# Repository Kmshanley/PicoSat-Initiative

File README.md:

# PicoSat-Initiative

The Wentworth Picosat initiative is a group at Wentworth Institute of technology dedicated to making a pocket cube satellite capable of earth observation from LEO.

The pocket cube standard requires satellites to be 5x5x5cm and under 250 grams. Upon completion of this Wentworth PicoSat it will become one of the smallest satellites capable of high resolution imagery from LEO.

* **Homepage:** <https://picosat.notion.site>
* **Communication:** <https://discord.gg/C9kFq642a>

Organization
------------------------
This repository is divided into two primary sections:
### Test
> Contains all firmware related to testing boards or individual components.
### Flight
> Contains the development for the main flight firmware that will be deployed in space.

Getting Started
------------------------
The easiest way to get started is by using the Stm32CubeIDE.

Downloadable here: https://www.st.com/en/development-tools/stm32cubeide.html

From here you should be able to import the various project files (.ioc) and CubeIDE will handle setup, build tools, and compilation.

High Level Overview
------------------------

The Satellite is composed of several **subsystems**:

* Onboard Computer System (OBC)
    * Responsible for handling commands from the ground station
    * Running ADCS algorithms
    * Commanding the image sensor to take pictures
        * Compressing and Storing these pictures until downlink
    * Gathering telemetry from sensors
        * Feeding telemetry to the appropriate subsystem
            * I.e. LUX sensor data to ADCS
    * Managing Satellite Energy consumption
        * Monitoring battery health and determining wakeup periods
* Electrical Power System (EPS)
    * Responsible for generating, storing, and regulating electrical power
* Communications (COMMS)
    * Responsible for uplink and downlink to ground station 
* Attitude Control and determination (ADCS)
    * Responsible for determining the attitude (rotation) of the satellite
    * Responsible for executing rotational maneuvers

Hardware Overview
------------------------

Contact
------------------------
You can join our discord with the link above or contact us directly via email:

OBC Team Lead (Kieran Shanley): <kmshanley01@gmail.com>

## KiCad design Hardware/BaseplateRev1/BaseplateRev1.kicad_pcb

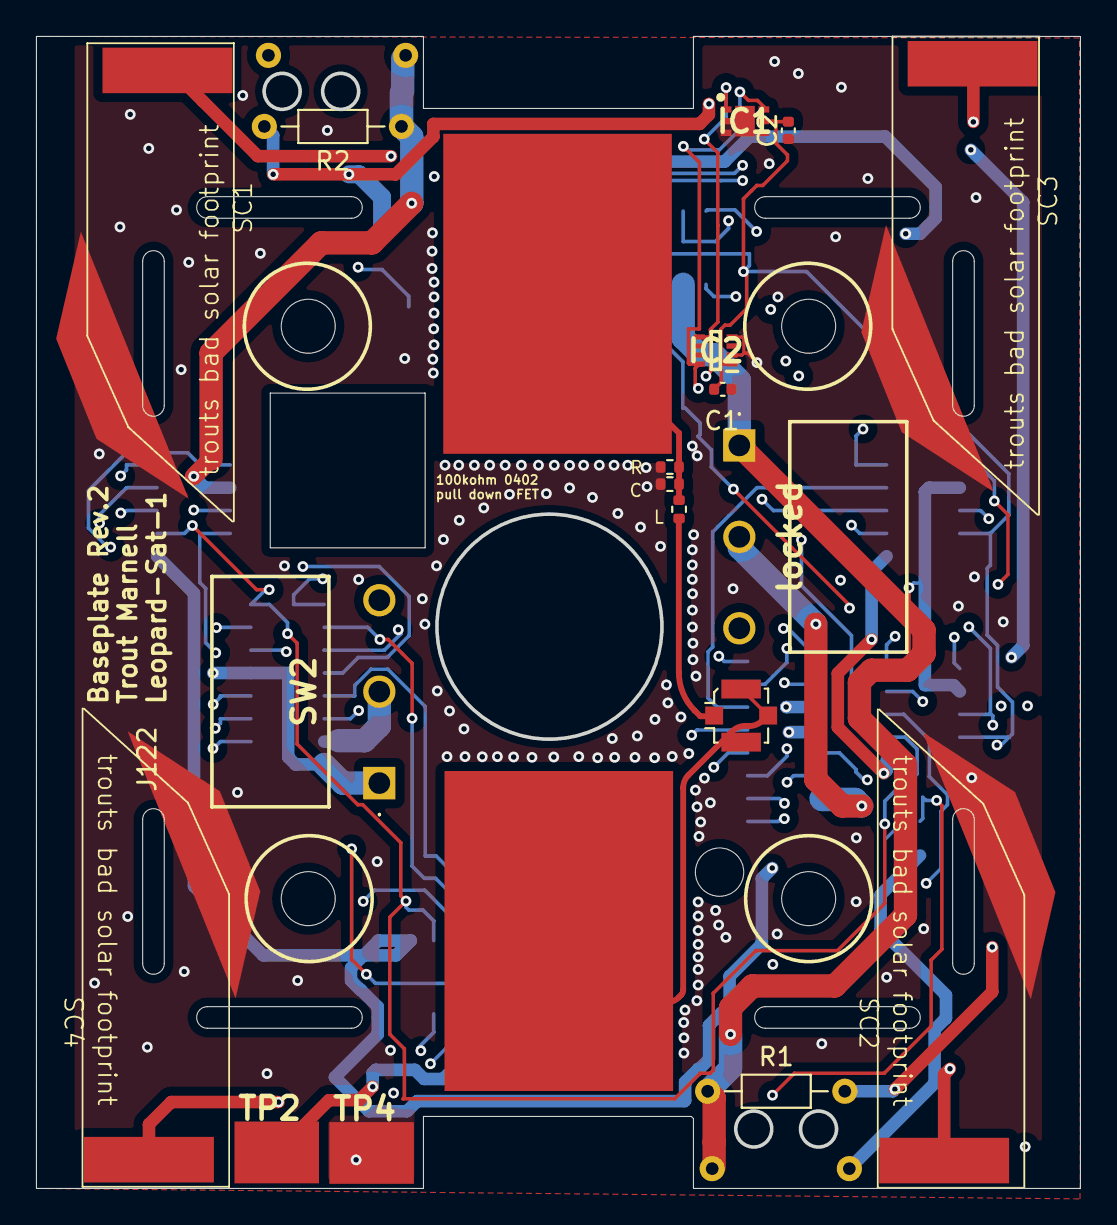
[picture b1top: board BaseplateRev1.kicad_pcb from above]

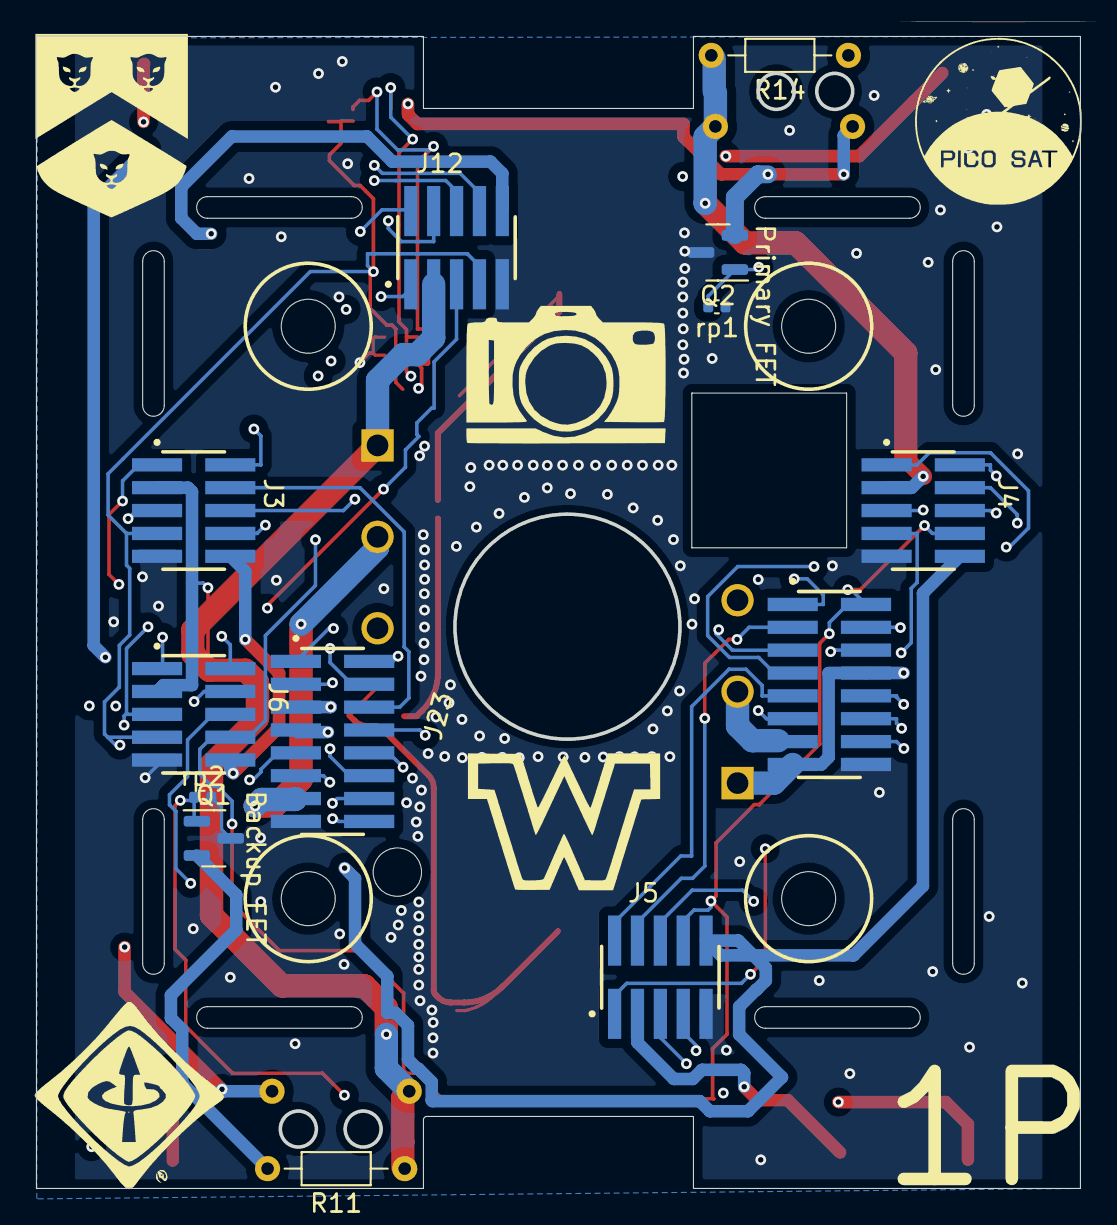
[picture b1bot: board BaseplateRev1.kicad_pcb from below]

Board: 4 copper layers, 57.9 x 63.9 mm, 33 parts (13 on the bottom side), 33 nets.

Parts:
C1, C2: 0.1uF; C_0402_1005Metric
IC1: TMP117MAIDRVR; SON65P200X200X80-7N
IC2: OPT4048DTSR; SOTFL50P190X60-8N
J3, J4, J5, J6, J12: FTSH-105-XX-X-DV; SAMTEC_FTSH-105-XX-X-DV
J8: Conn_Coaxial; U.FL_Molex_MCRF_73412-0110_Vertical
J23, J122: FLE-108-01-XX-DV; SAMTEC_FW-08-03-G-D-335-065
Q1, Q2: 2N7002; SOT-23
R1, R2, R11, R14: R_Small_US; R_Axial_DIN0204_L3.6mm_D1.6mm_P7.62mm_Horizontal
REF5554: R_0402_1005Metric
REFW: R_0402_1005Metric
REFinduc: R_0402_1005Metric
SC1, SC2, SC3, SC4: Solar_Cell; solar
SW2: SW_SPDT; D2FA1
TP2, TP4: TestPoint; 5016
U1, U2: antenna
locked: SW_SPDT; D2FA1
rp1, rp2: 100k; C_0402_1005Metric

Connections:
1.8V: C1.2, C2.2, IC1.5 (V+), IC2.1 (VDD), J3.07, J4.07, J5.07, J6.07, J12.07, J23.11, J122.14
Battery +: J3.03, J4.03, J5.03, J6.03, J12.03, J122.08, J122.15, R1.1, R2.1, R11.1, R14.2, SW2.1 (A), TP2.1, locked.1 (A)
Coaxout: J8.1 (In), REFinduc.1
DRV ENABLE 1: J4.04, J122.01
DRV ENABLE 2: J5.04, J122.03
DRV ENABLE 3: J6.04, J23.10
DRV ENABLE 4: J12.04, J23.08
DRV ENABLE 5: J3.04, J23.06
GND: C1.1, C2.1, IC1.2 (GND), IC1.3 (ALERT), IC1.4 (ADD0), IC1.7 (EP), IC2.2 (ADDR), IC2.4 (GND), J3.09, J4.09, J5.09, J6.09, J12.09, J23.15, J122.16, Q1.3 (D), Q2.3 (D), REF5554.1, REFW.1, SC1.2 (-), SC2.2 (-), SC3.2 (-), SC4.2 (-), TP4.1, rp1.1, rp2.2
MCU ENABLE 1: J122.07, Q2.1 (G), rp1.2
MCU ENABLE 2: J122.05, Q1.1 (G), rp2.1
MPPT ENABLE: J3.06, J4.06, J5.06, J6.06, J12.06, J122.06
unnamed: Q1.2 (S), R11.2, R14.1
unnamed: Q2.2 (S), R1.2, R2.2
PWM1(1): J4.01, J122.10
PWM1(2): J5.01, J122.11
PWM1(3): J6.01, J23.02
PWM1(4): J12.01, J23.03
PWM1(5): J3.01, J23.09
PWM2(1): J4.02, J122.12
PWM2(2): J5.02, J122.09
PWM2(3): J6.02, J23.04
PWM2(4): J12.02, J23.01
PWM2(5): J3.02, J23.16
RF ANTENNA: REF5554.2, REFW.2, REFinduc.2, U2.1 (RF_IN)
SCL(1): J4.08, J5.08, J6.08, J12.08, J122.02
SCL(2): IC1.1 (SCL), IC2.5 (SCL), J3.08, J23.12
SDA(1): J4.05, J5.05, J6.05, J12.05, J122.04
SDA(2): IC1.6 (SDA), IC2.8 (SDA), J3.05, J23.14
VBAT+: J23.13, J122.13, SW2.2 (B), locked.2 (B)
VMPPT: J3.10, J4.10, J5.10, J6.10, J12.10, J23.07
Vsolar: J23.05, SC1.1 (+), SC2.1 (+), SC3.1 (+), SC4.1 (+)
rfgnd: J8.2 (Ext), U1.1 (RF_IN)

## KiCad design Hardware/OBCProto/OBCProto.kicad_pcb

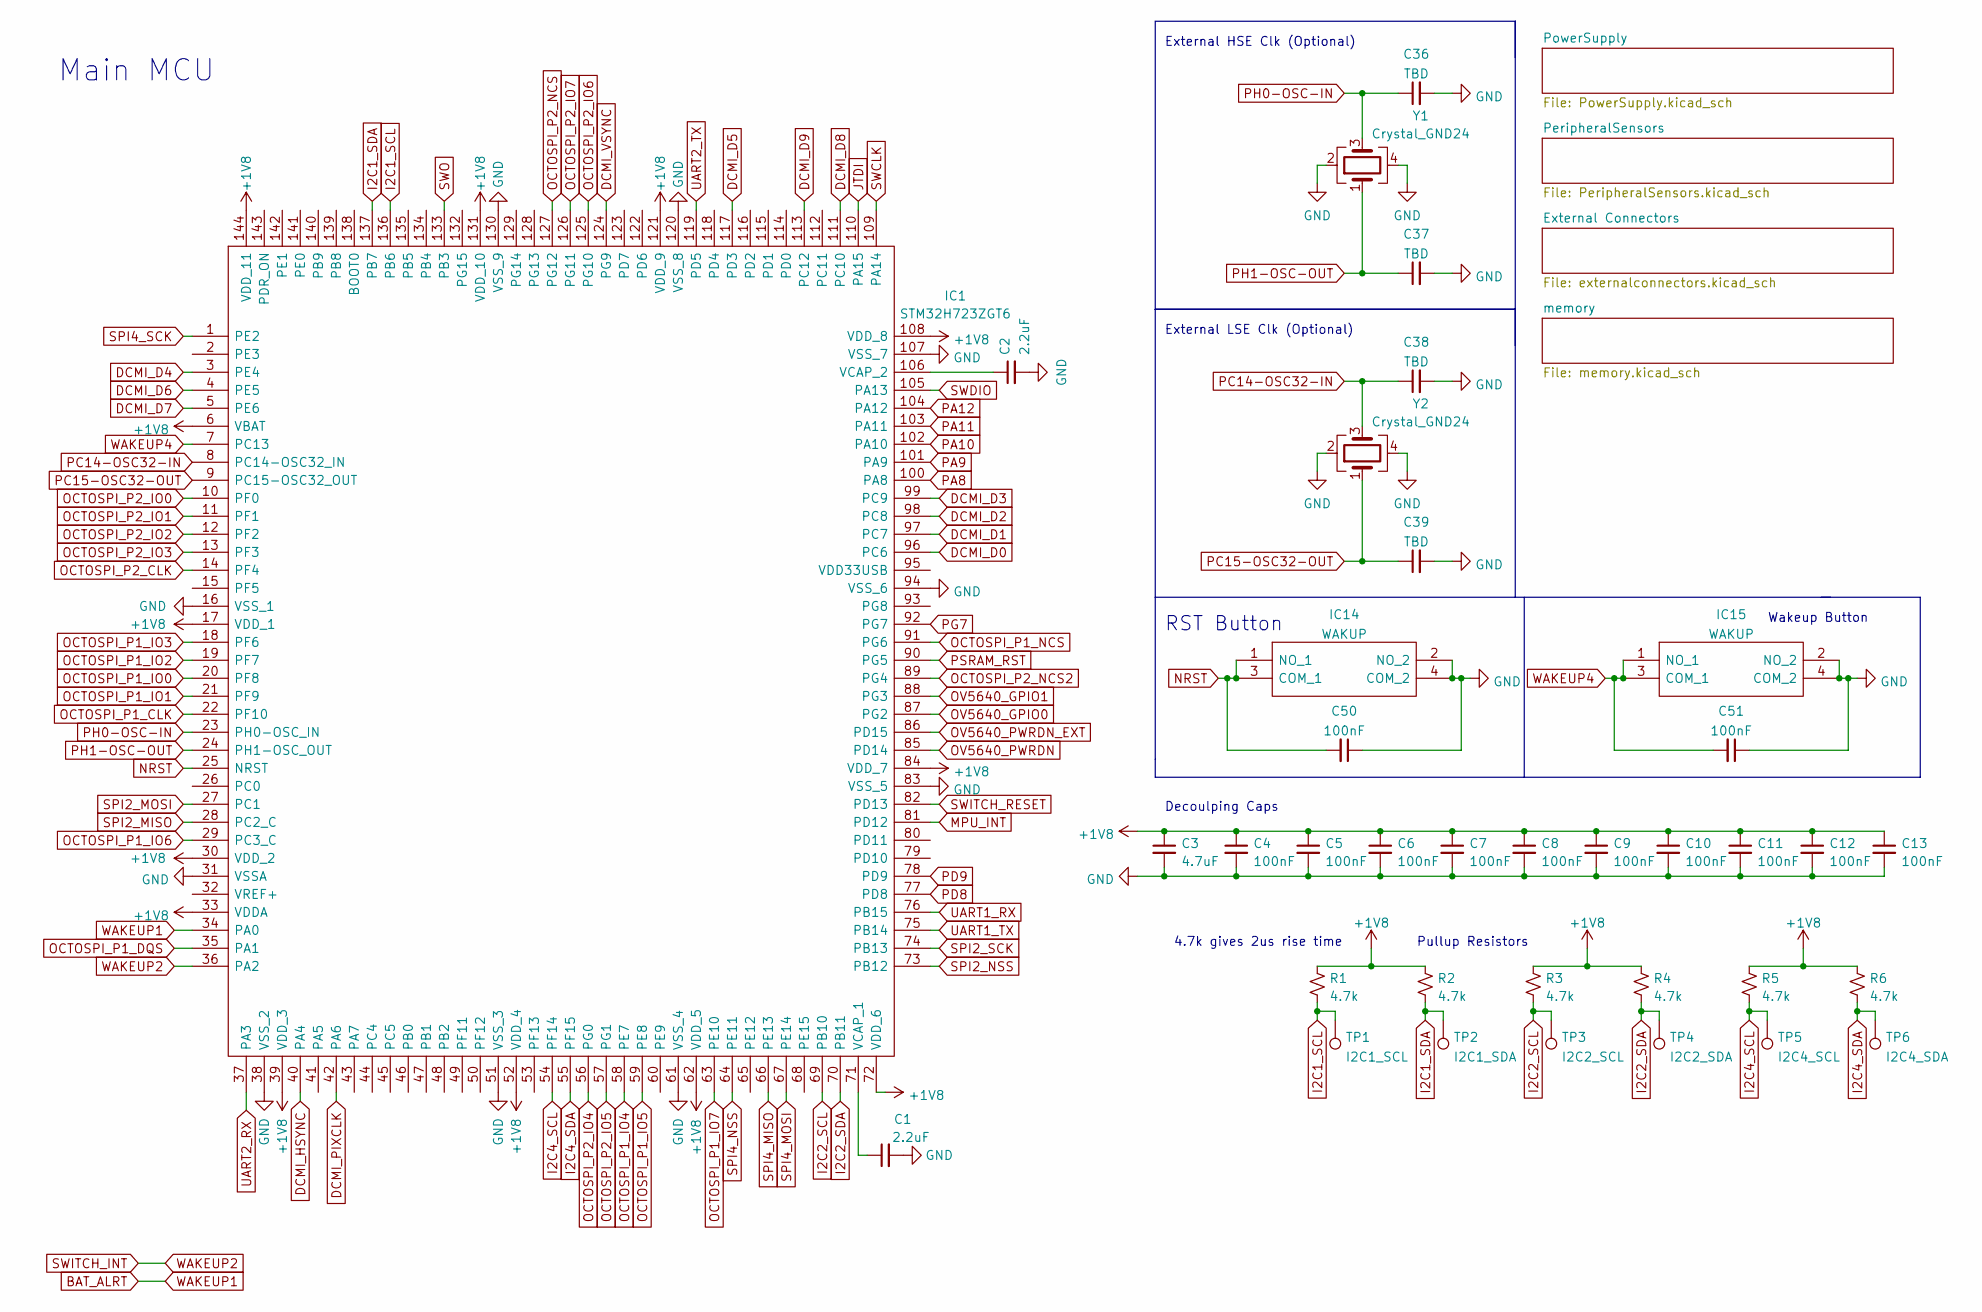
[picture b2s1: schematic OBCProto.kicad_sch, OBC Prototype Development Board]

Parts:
C1, C2: 2.2uF; C_0402_1005Metric
C3: 4.7uF; C_0402_1005Metric
C4, C5, C6, C7, C8, C9, C10, C11, C12, C13, C50, C51: 100nF; C_0402_1005Metric
C36, C37, C38, C39: TBD; C_0402_1005Metric
IC1: STM32H723ZGT6; QFP50P2200X2200X160-144N; Mouser Part Number 511-STM32H723ZGT6
IC14, IC15: WAKUP; TS046675BK160SMT; Mouser Part Number 179-TS046675BK160SMT
R1, R2, R3, R4, R5, R6: 4.7k; R_0402_1005Metric
TP1: I2C1_SCL; TestPoint_Pad_2.0x2.0mm
TP2: I2C1_SDA; TestPoint_Pad_2.0x2.0mm
TP3: I2C2_SCL; TestPoint_Pad_2.0x2.0mm
TP4: I2C2_SDA; TestPoint_Pad_2.0x2.0mm
TP5: I2C4_SCL; TestPoint_Pad_2.0x2.0mm
TP6: I2C4_SDA; TestPoint_Pad_2.0x2.0mm
Y1, Y2: Crystal_GND24; Crystal_SMD_2520-4Pin_2.5x2.0mm

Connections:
+1V8: C3.1, C4.1, C5.1, C6.1, C7.1, C8.1, C9.1, C10.1, C11.1, C12.1, C13.1, IC1.6 (VBAT), IC1.17 (VDD_1), IC1.30 (VDD_2), IC1.33 (VDDA), IC1.39 (VDD_3), IC1.52 (VDD_4), IC1.62 (VDD_5), IC1.72 (VDD_6), IC1.84 (VDD_7), IC1.108 (VDD_8), IC1.121 (VDD_9), IC1.131 (VDD_10), IC1.144 (VDD_11), R1.1, R2.1, R3.1, R4.1, R5.1, R6.1; also elsewhere on the board
BAT_ALRT: IC1.34 (PA0)
DCMI_D0: IC1.96 (PC6); also elsewhere on the board
DCMI_D1: IC1.97 (PC7); also elsewhere on the board
DCMI_D2: IC1.98 (PC8); also elsewhere on the board
DCMI_D3: IC1.99 (PC9); also elsewhere on the board
DCMI_D4: IC1.3 (PE4); also elsewhere on the board
DCMI_D5: IC1.117 (PD3); also elsewhere on the board
DCMI_D6: IC1.4 (PE5); also elsewhere on the board
DCMI_D7: IC1.5 (PE6); also elsewhere on the board
DCMI_D8: IC1.111 (PC10); also elsewhere on the board
DCMI_D9: IC1.113 (PC12); also elsewhere on the board
DCMI_HSYNC: IC1.40 (PA4); also elsewhere on the board
DCMI_PIXCLK: IC1.42 (PA6); also elsewhere on the board
DCMI_VSYNC: IC1.124 (PG9); also elsewhere on the board
GND: C1.2, C2.2, C3.2, C4.2, C5.2, C6.2, C7.2, C8.2, C9.2, C10.2, C11.2, C12.2, C13.2, C36.2, C37.2, C38.2, C39.2, C50.1, C51.1, IC1.16 (VSS_1), IC1.31 (VSSA), IC1.38 (VSS_2), IC1.51 (VSS_3), IC1.61 (VSS_4), IC1.83 (VSS_5), IC1.94 (VSS_6), IC1.107 (VSS_7), IC1.120 (VSS_8), IC1.130 (VSS_9), IC14.2 (NO_2), IC14.4 (COM_2), IC15.2 (NO_2), IC15.4 (COM_2), Y1.2, Y1.4, Y2.2, Y2.4; also elsewhere on the board
I2C1_SCL: IC1.136 (PB6), R1.2, TP1.1; also elsewhere on the board
I2C1_SDA: IC1.137 (PB7), R2.2, TP2.1; also elsewhere on the board
I2C2_SCL: IC1.69 (PB10), R3.2, TP3.1; also elsewhere on the board
I2C2_SDA: IC1.70 (PB11), R4.2, TP4.1; also elsewhere on the board
I2C4_SCL: IC1.54 (PF14), R5.2, TP5.1; also elsewhere on the board
I2C4_SDA: IC1.55 (PF15), R6.2, TP6.1; also elsewhere on the board
JTDI: IC1.110 (PA15); also elsewhere on the board
MPU_INT: IC1.81 (PD12); also elsewhere on the board
NRST: C50.2, IC1.25 (NRST), IC14.1 (NO_1), IC14.3 (COM_1); also elsewhere on the board
unnamed: C1.1, IC1.71 (VCAP_1)
unnamed: C2.1, IC1.106 (VCAP_2)
OCTOSPI_P1_CLK: IC1.22 (PF10); also elsewhere on the board
OCTOSPI_P1_DQS: IC1.35 (PA1); also elsewhere on the board
OCTOSPI_P1_IO0: IC1.20 (PF8); also elsewhere on the board
OCTOSPI_P1_IO1: IC1.21 (PF9); also elsewhere on the board
OCTOSPI_P1_IO2: IC1.19 (PF7); also elsewhere on the board
OCTOSPI_P1_IO3: IC1.18 (PF6); also elsewhere on the board
OCTOSPI_P1_IO4: IC1.58 (PE7); also elsewhere on the board
OCTOSPI_P1_IO5: IC1.59 (PE8); also elsewhere on the board
OCTOSPI_P1_IO6: IC1.29 (PC3_C); also elsewhere on the board
OCTOSPI_P1_IO7: IC1.63 (PE10); also elsewhere on the board
OCTOSPI_P1_NCS: IC1.91 (PG6); also elsewhere on the board
OCTOSPI_P2_CLK: IC1.14 (PF4); also elsewhere on the board
OCTOSPI_P2_IO0: IC1.10 (PF0); also elsewhere on the board
OCTOSPI_P2_IO1: IC1.11 (PF1); also elsewhere on the board
OCTOSPI_P2_IO2: IC1.12 (PF2); also elsewhere on the board
OCTOSPI_P2_IO3: IC1.13 (PF3); also elsewhere on the board
OCTOSPI_P2_IO4: IC1.56 (PG0); also elsewhere on the board
OCTOSPI_P2_IO5: IC1.57 (PG1); also elsewhere on the board
OCTOSPI_P2_IO6: IC1.125 (PG10); also elsewhere on the board
OCTOSPI_P2_IO7: IC1.126 (PG11)
OCTOSPI_P2_NCS: IC1.127 (PG12); also elsewhere on the board
OCTOSPI_P2_NCS2: IC1.89 (PG4); also elsewhere on the board
OV5640_GPIO0: IC1.87 (PG2); also elsewhere on the board
OV5640_GPIO1: IC1.88 (PG3); also elsewhere on the board
OV5640_PWRDN: IC1.85 (PD14); also elsewhere on the board
OV5640_PWRDN_EXT: IC1.86 (PD15); also elsewhere on the board
PA8: IC1.100 (PA8); also elsewhere on the board
PA9: IC1.101 (PA9); also elsewhere on the board
PA10: IC1.102 (PA10); also elsewhere on the board
PA11: IC1.103 (PA11); also elsewhere on the board
PA12: IC1.104 (PA12); also elsewhere on the board
PC14-OSC32-IN: C38.1, IC1.8 (PC14-OSC32_IN), Y2.3
PC15-OSC32-OUT: C39.1, IC1.9 (PC15-OSC32_OUT), Y2.1
PD8: IC1.77 (PD8); also elsewhere on the board
PD9: IC1.78 (PD9); also elsewhere on the board
PG7: IC1.92 (PG7); also elsewhere on the board
PH0-OSC-IN: C36.1, IC1.23 (PH0-OSC_IN), Y1.3
PH1-OSC-OUT: C37.1, IC1.24 (PH1-OSC_OUT), Y1.1
PSRAM_RST: IC1.90 (PG5); also elsewhere on the board
SPI2_MISO: IC1.28 (PC2_C); also elsewhere on the board
SPI2_MOSI: IC1.27 (PC1); also elsewhere on the board
SPI2_NSS: IC1.73 (PB12); also elsewhere on the board
SPI2_SCK: IC1.74 (PB13); also elsewhere on the board
SPI4_MISO: IC1.66 (PE13); also elsewhere on the board
SPI4_MOSI: IC1.67 (PE14); also elsewhere on the board
SPI4_NSS: IC1.64 (PE11); also elsewhere on the board
SPI4_SCK: IC1.1 (PE2); also elsewhere on the board
SWCLK: IC1.109 (PA14); also elsewhere on the board
SWDIO: IC1.105 (PA13); also elsewhere on the board
SWITCH_INT: IC1.36 (PA2); also elsewhere on the board
SWITCH_RESET: IC1.82 (PD13); also elsewhere on the board
SWO: IC1.133 (PB3); also elsewhere on the board
UART1_RX: IC1.76 (PB15); also elsewhere on the board
UART1_TX: IC1.75 (PB14); also elsewhere on the board
UART2_RX: IC1.37 (PA3); also elsewhere on the board
UART2_TX: IC1.119 (PD5); also elsewhere on the board
WAKEUP4: C51.2, IC1.7 (PC13), IC15.1 (NO_1), IC15.3 (COM_1)

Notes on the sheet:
Main MCU
RST Button
Wakeup Button
4.7k gives 2us rise time
Pullup Resistors
External HSE Clk (Optional)
External LSE Clk (Optional)
Decoulping Caps

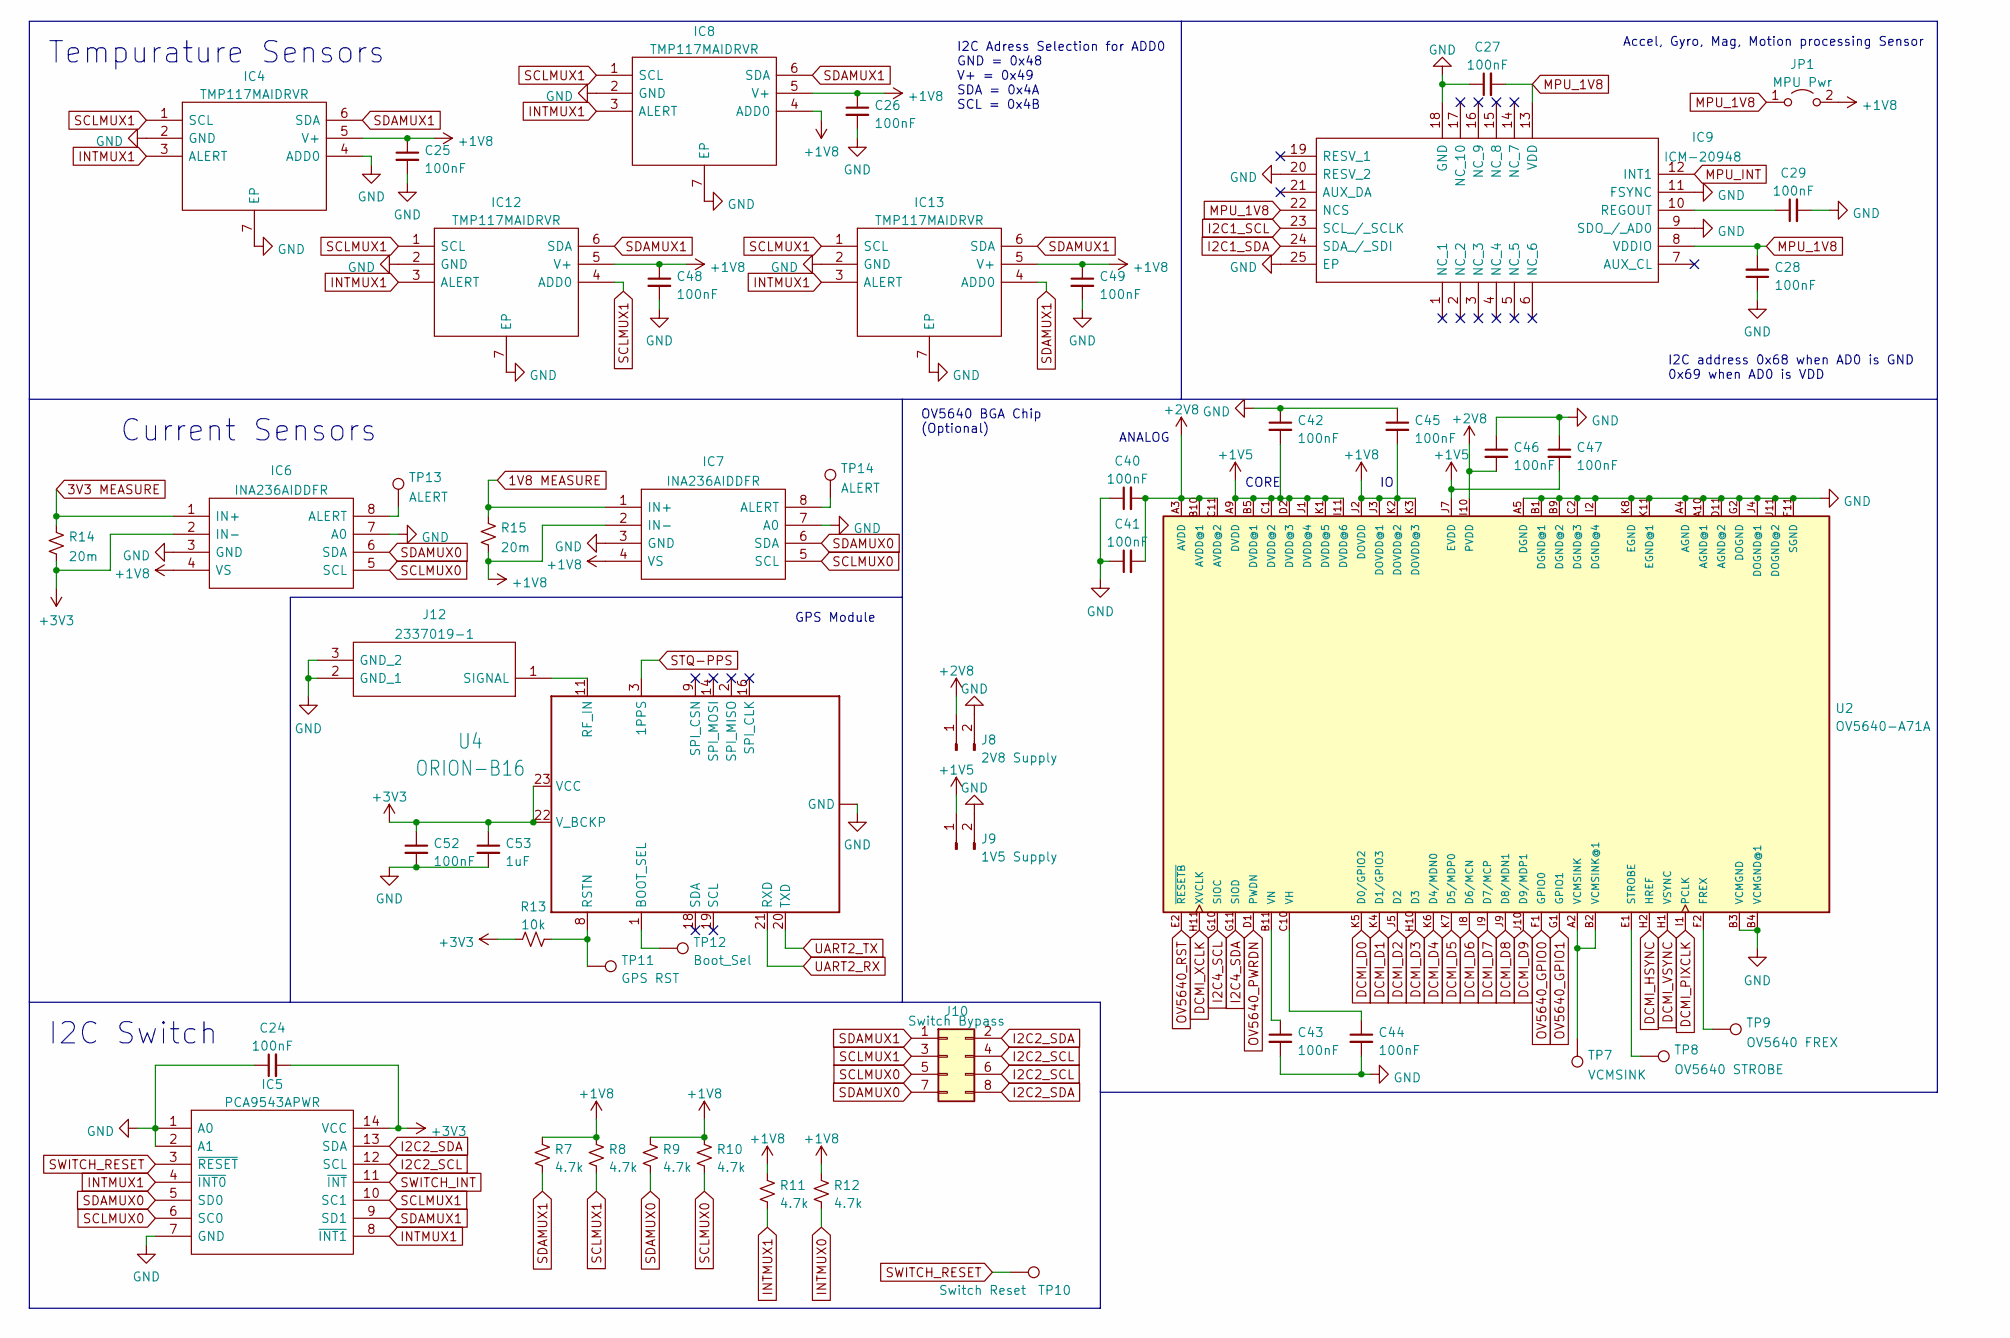
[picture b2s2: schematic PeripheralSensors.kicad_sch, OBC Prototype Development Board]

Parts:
C24, C25, C26, C27, C28, C29, C40, C41, C42, C43, C44, C45, C46, C47, C48, C49, C52: 100nF; C_0402_1005Metric
C53: 1uF; C_0402_1005Metric
IC4, IC8, IC12, IC13: TMP117MAIDRVR; SON65P200X200X80-7N; Mouser Part Number 595-TMP117MAIDRVR
IC5: PCA9543APWR; SOP65P640X120-14N; Mouser Part Number 595-PCA9543APWR
IC6, IC7: INA236AIDDFR; SOP65P280X110-8N; Manufacturer_Part_Number INA236AIDDFR; Mouser Part Number 595-INA236AIDDFR
IC9: ICM-20948; QFN40P300X300X105-25N-D; Mouser Part Number 410-ICM-20948
J8: 2V8 Supply; PinHeader_1x02_P2.54mm_Vertical
J9: 1V5 Supply; PinHeader_1x02_P2.54mm_Vertical
J10: Switch Bypass; PinHeader_2x04_P2.54mm_Vertical
J12: 2337019-1; 23370191; Mouser Part Number 571-2337019-1
JP1: MPU Pwr; PinHeader_1x02_P2.54mm_Vertical
R7, R8, R9, R10, R11, R12: 4.7k; R_0402_1005Metric
R13: 10k; R_0402_1005Metric
R14, R15: 20m; R_1020_2550Metric
TP7: VCMSINK; TestPoint_Pad_2.0x2.0mm
TP8: OV5640 STROBE; TestPoint_Pad_2.0x2.0mm
TP9: OV5640 FREX; TestPoint_Pad_2.0x2.0mm
TP10: Switch Reset; TestPoint_Pad_2.0x2.0mm
TP11: GPS RST; TestPoint_Pad_1.5x1.5mm
TP12: Boot_Sel; TestPoint_Pad_1.5x1.5mm
TP13, TP14: ALERT; TestPoint_Pad_1.0x1.0mm
U2: OV5640-A71A; BGA71C50P11X11_598X584X81
U4: ORION-B16; U-SkyTraq-ORION-B16

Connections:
1V8 MEASURE: IC7.1 (IN+), R15.1; also elsewhere on the board
3V3 MEASURE: IC6.1 (IN+), R14.1; also elsewhere on the board
+1V5: C42.2, C47.2, J9.1, U2.A9 (DVDD), U2.B5 (DVDD@1), U2.C1 (DVDD@2), U2.D2 (DVDD@3), U2.I11 (DVDD@6), U2.J1 (DVDD@4), U2.J7 (EVDD), U2.K1 (DVDD@5)
+1V8: C25.1, C26.1, C45.2, C48.1, C49.1, IC4.5 (V+), IC6.4 (VS), IC7.2 (IN-), IC7.4 (VS), IC8.4 (ADD0), IC8.5 (V+), IC12.5 (V+), IC13.5 (V+), JP1.2 (B), R7.1, R8.1, R9.1, R10.1, R11.1, R12.1, R15.2, U2.J2 (DOVDD), U2.J3 (DOVDD@1), U2.K2 (DOVDD@2), U2.K3 (DOVDD@3); also elsewhere on the board
+2V8: C40.2, C41.2, C46.2, J8.1, U2.A3 (AVDD), U2.B10 (AVDD@1), U2.C11 (AVDD@2), U2.I10 (PVDD)
+3V3: C24.2, C52.1, C53.1, IC5.14 (VCC), IC6.2 (IN-), R13.1, R14.2, U4.22 (V_BCKP), U4.23 (VCC); also elsewhere on the board
DCMI_D0: U2.K5 (D0/GPIO2); also elsewhere on the board
DCMI_D1: U2.K4 (D1/GPIO3); also elsewhere on the board
DCMI_D2: U2.J5 (D2); also elsewhere on the board
DCMI_D3: U2.H10 (D3); also elsewhere on the board
DCMI_D4: U2.K6 (D4/MDN0); also elsewhere on the board
DCMI_D5: U2.K7 (D5/MDP0); also elsewhere on the board
DCMI_D6: U2.I8 (D6/MCN); also elsewhere on the board
DCMI_D7: U2.I9 (D7/MCP); also elsewhere on the board
DCMI_D8: U2.J9 (D8/MDN1); also elsewhere on the board
DCMI_D9: U2.J10 (D9/MDP1); also elsewhere on the board
DCMI_HSYNC: U2.H2 (HREF); also elsewhere on the board
DCMI_PIXCLK: U2.I1 (PCLK); also elsewhere on the board
DCMI_VSYNC: U2.H1 (VSYNC); also elsewhere on the board
DCMI_XCLK: U2.H11 (XVCLK); also elsewhere on the board
GND: C24.1, C25.2, C26.2, C27.1, C28.1, C29.2, C40.1, C41.1, C42.1, C43.2, C44.2, C45.1, C46.1, C47.1, C48.2, C49.2, C52.2, C53.2, IC4.2 (GND), IC4.4 (ADD0), IC4.7 (EP), IC5.1 (A0), IC5.2 (A1), IC5.7 (GND), IC6.3 (GND), IC6.7 (A0), IC7.3 (GND), IC7.7 (A0), IC8.2 (GND), IC8.7 (EP), IC9.9 (SDO_/_AD0), IC9.11 (FSYNC), IC9.18 (GND), IC9.20 (RESV_2), IC9.25 (EP), IC12.2 (GND), IC12.7 (EP), IC13.2 (GND), IC13.7 (EP), J8.2, J9.2, J12.2 (GND_1), J12.3 (GND_2), U2.A4 (AGND), U2.A5 (DGND), U2.A10 (AGND@1), U2.B1 (DGND@1), U2.B3 (VCMGND), U2.B4 (VCMGND@1), U2.B9 (DGND@2), U2.C2 (DGND@3), U2.D11 (AGND@2), U2.F11 (SGND), U2.G2 (DOGND), U2.I2 (DGND@4), U2.J4 (DOGND@1), U2.J11 (DOGND@2), U2.K8 (EGND), U2.K11 (EGND@1), U4.10 (GND), U4.12 (GND), U4.13 (GND), U4.24 (GND); also elsewhere on the board
I2C1_SCL: IC9.23 (SCL_/_SCLK); also elsewhere on the board
I2C1_SDA: IC9.24 (SDA_/_SDI); also elsewhere on the board
I2C2_SCL: IC5.12 (SCL), J10.4, J10.6; also elsewhere on the board
I2C2_SDA: IC5.13 (SDA), J10.2, J10.8; also elsewhere on the board
I2C4_SCL: U2.G10 (SIOC); also elsewhere on the board
I2C4_SDA: U2.G11 (SIOD); also elsewhere on the board
INTMUX0: R12.2
INTMUX1: IC4.3 (ALERT), IC5.4 (~INT0), IC5.8 (~INT1), IC8.3 (ALERT), IC12.3 (ALERT), IC13.3 (ALERT), R11.2
MPU_1V8: C27.2, C28.2, IC9.8 (VDDIO), IC9.13 (VDD), IC9.22 (NCS), JP1.1 (A)
MPU_INT: IC9.12 (INT1); also elsewhere on the board
unnamed: C29.1, IC9.10 (REGOUT)
unnamed: C43.1, U2.B11 (VN)
unnamed: C44.1, U2.C10 (VH)
unnamed: IC6.8 (ALERT), TP13.1
unnamed: IC7.8 (ALERT), TP14.1
unnamed: J12.1 (SIGNAL), U4.11 (RF_IN)
unnamed: R13.2, TP11.1, U4.8 (RSTN)
unnamed: TP7.1, U2.A2 (VCMSINK), U2.B2 (VCMSINK@1)
unnamed: TP8.1, U2.E1 (STROBE)
unnamed: TP9.1, U2.F2 (FREX)
unnamed: TP12.1, U4.1 (BOOT_SEL)
OV5640_GPIO0: U2.F1 (GPIO0); also elsewhere on the board
OV5640_GPIO1: U2.G1 (GPIO1); also elsewhere on the board
OV5640_PWRDN: U2.D1 (PWDN); also elsewhere on the board
OV5640_RST: U2.E2 (~RESETB); also elsewhere on the board
SCLMUX0: IC5.6 (SC0), IC6.5 (SCL), IC7.5 (SCL), J10.5, R10.2
SCLMUX1: IC4.1 (SCL), IC5.10 (SC1), IC8.1 (SCL), IC12.1 (SCL), IC12.4 (ADD0), IC13.1 (SCL), J10.3, R8.2
SDAMUX0: IC5.5 (SD0), IC6.6 (SDA), IC7.6 (SDA), J10.7, R9.2
SDAMUX1: IC4.6 (SDA), IC5.9 (SD1), IC8.6 (SDA), IC12.6 (SDA), IC13.4 (ADD0), IC13.6 (SDA), J10.1, R7.2
STQ-PPS: U4.3 (1PPS)
SWITCH_INT: IC5.11 (~INT); also elsewhere on the board
SWITCH_RESET: IC5.3 (~RESET), TP10.1; also elsewhere on the board
UART2_RX: U4.21 (RXD); also elsewhere on the board
UART2_TX: U4.20 (TXD); also elsewhere on the board

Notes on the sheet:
ANALOG
Accel, Gyro, Mag, Motion processing Sensor
I2C Adress Selection for ADD0 GND = 0x48 V+ = 0x49 SDA = 0x4A SCL = 0x4B
Tempurature Sensors
I2C address 0x68 when AD0 is GND 0x69 when AD0 is VDD
OV5640 BGA Chip (Optional)
GPS Module
Current Sensors
I2C Switch
CORE

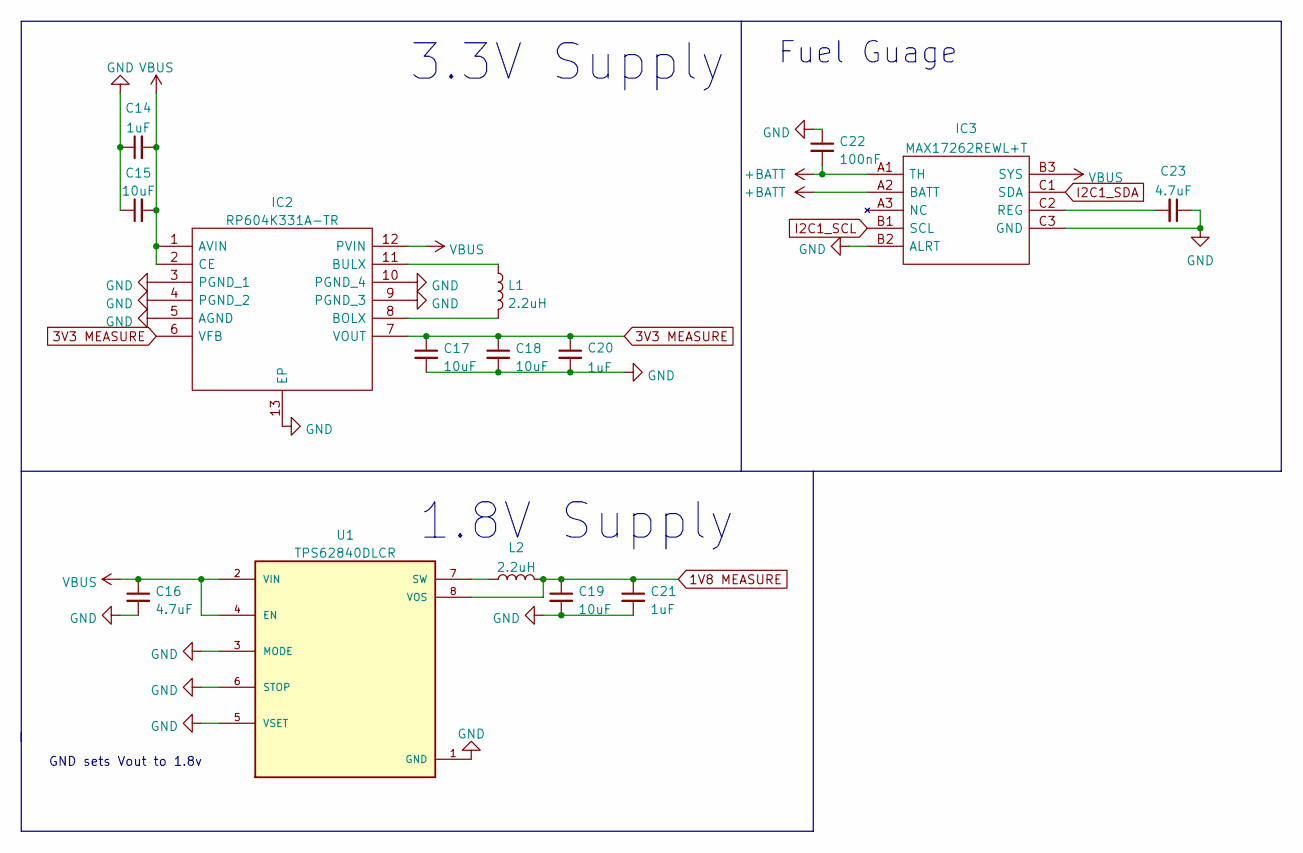
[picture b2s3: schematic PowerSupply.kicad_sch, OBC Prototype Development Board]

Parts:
C14, C20, C21: 1uF; C_0402_1005Metric
C15, C17, C18, C19: 10uF; C_0402_1005Metric
C16, C23: 4.7uF; C_0402_1005Metric
C22: 100nF; C_0402_1005Metric
IC2: RP604K331A-TR; SON50P270X300X60-13N; Mouser Part Number 848-RP604K331A-TR
IC3: MAX17262REWL+T; BGA9C40P3X3_147X145X69; Mouser Part Number 700-MAX17262REWL+T
L1, L2: 2.2uH; L_1008_2520Metric
U1: TPS62840DLCR; SON50P200X150X100-8N

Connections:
1V8 MEASURE: C19.1, C21.1, L2.2, U1.8 (VOS); also elsewhere on the board
3V3 MEASURE: C17.1, C18.1, C20.1, IC2.6 (VFB), IC2.7 (VOUT); also elsewhere on the board
+BATT: C22.2, IC3.A1 (TH), IC3.A2 (BATT); also elsewhere on the board
GND: C14.1, C15.1, C16.2, C17.2, C18.2, C19.2, C20.2, C21.2, C22.1, C23.1, IC2.3 (PGND_1), IC2.4 (PGND_2), IC2.5 (AGND), IC2.9 (PGND_3), IC2.10 (PGND_4), IC2.13 (EP), IC3.B2 (ALRT), IC3.C3 (GND), U1.1 (GND), U1.3 (MODE), U1.5 (VSET), U1.6 (STOP); also elsewhere on the board
I2C1_SCL: IC3.B1 (SCL); also elsewhere on the board
I2C1_SDA: IC3.C1 (SDA); also elsewhere on the board
unnamed: C23.2, IC3.C2 (REG)
unnamed: IC2.8 (BOLX), L1.2
unnamed: IC2.11 (BULX), L1.1
unnamed: L2.1, U1.7 (SW)
VBUS: C14.2, C15.2, C16.1, IC2.1 (AVIN), IC2.2 (CE), IC2.12 (PVIN), IC3.B3 (SYS), U1.2 (VIN), U1.4 (EN); also elsewhere on the board

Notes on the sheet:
3.3V Supply
1.8V Supply
GND sets Vout to 1.8v
Fuel Guage

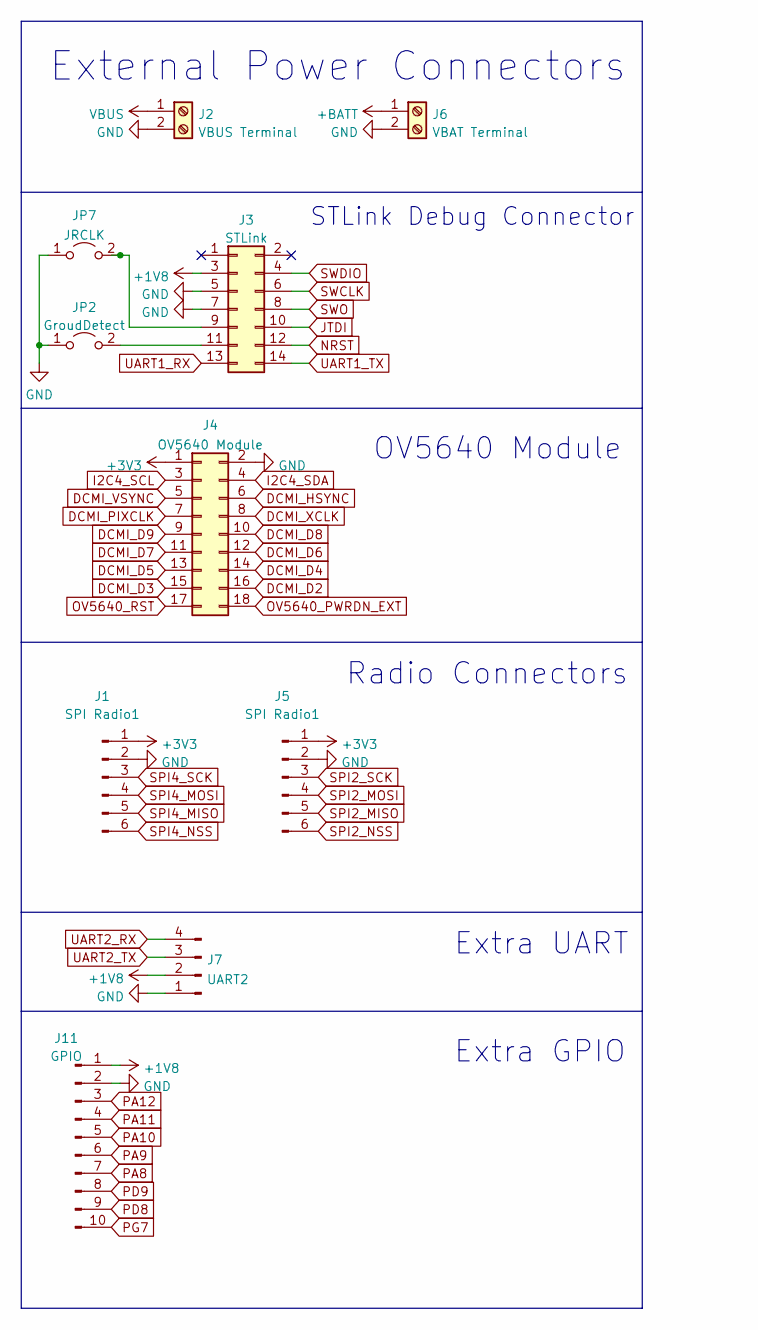
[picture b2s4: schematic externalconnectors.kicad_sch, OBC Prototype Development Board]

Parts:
J1, J5: SPI Radio1; PinHeader_1x06_P2.54mm_Vertical
J2: VBUS Terminal; TerminalBlock_TE_282834-2_1x02_P2.54mm_Horizontal
J3: STLink; PinHeader_2x07_P1.27mm_Vertical
J4: OV5640 Module; PinHeader_2x09_P2.54mm_Vertical
J6: VBAT Terminal; TerminalBlock_TE_282834-2_1x02_P2.54mm_Horizontal
J7: UART2; PinHeader_1x04_P2.54mm_Vertical
J11: GPIO; PinHeader_1x10_P2.54mm_Vertical
JP2: GroudDetect; PinHeader_1x02_P2.54mm_Vertical
JP7: JRCLK; PinHeader_1x02_P2.54mm_Vertical

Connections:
+1V8: J3.3, J7.2, J11.1; also elsewhere on the board
+3V3: J1.1, J4.1, J5.1; also elsewhere on the board
+BATT: J6.1; also elsewhere on the board
DCMI_D2: J4.16; also elsewhere on the board
DCMI_D3: J4.15; also elsewhere on the board
DCMI_D4: J4.14; also elsewhere on the board
DCMI_D5: J4.13; also elsewhere on the board
DCMI_D6: J4.12; also elsewhere on the board
DCMI_D7: J4.11; also elsewhere on the board
DCMI_D8: J4.10; also elsewhere on the board
DCMI_D9: J4.9; also elsewhere on the board
DCMI_HSYNC: J4.6; also elsewhere on the board
DCMI_PIXCLK: J4.7; also elsewhere on the board
DCMI_VSYNC: J4.5; also elsewhere on the board
DCMI_XCLK: J4.8; also elsewhere on the board
GND: J1.2, J2.2, J3.5, J3.7, J4.2, J5.2, J6.2, J7.1, J11.2, JP2.1 (A), JP7.1 (A); also elsewhere on the board
I2C4_SCL: J4.3; also elsewhere on the board
I2C4_SDA: J4.4; also elsewhere on the board
JTDI: J3.10; also elsewhere on the board
NRST: J3.12; also elsewhere on the board
unnamed: J3.9, JP7.2 (B)
unnamed: J3.11, JP2.2 (B)
OV5640_PWRDN_EXT: J4.18; also elsewhere on the board
OV5640_RST: J4.17; also elsewhere on the board
PA8: J11.7; also elsewhere on the board
PA9: J11.6; also elsewhere on the board
PA10: J11.5; also elsewhere on the board
PA11: J11.4; also elsewhere on the board
PA12: J11.3; also elsewhere on the board
PD8: J11.9; also elsewhere on the board
PD9: J11.8; also elsewhere on the board
PG7: J11.10; also elsewhere on the board
SPI2_MISO: J5.5; also elsewhere on the board
SPI2_MOSI: J5.4; also elsewhere on the board
SPI2_NSS: J5.6; also elsewhere on the board
SPI2_SCK: J5.3; also elsewhere on the board
SPI4_MISO: J1.5; also elsewhere on the board
SPI4_MOSI: J1.4; also elsewhere on the board
SPI4_NSS: J1.6; also elsewhere on the board
SPI4_SCK: J1.3; also elsewhere on the board
SWCLK: J3.6; also elsewhere on the board
SWDIO: J3.4; also elsewhere on the board
SWO: J3.8; also elsewhere on the board
UART1_RX: J3.13; also elsewhere on the board
UART1_TX: J3.14; also elsewhere on the board
UART2_RX: J7.4; also elsewhere on the board
UART2_TX: J7.3; also elsewhere on the board
VBUS: J2.1; also elsewhere on the board

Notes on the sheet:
Extra UART
OV5640 Module
STLink Debug Connector
Radio Connectors
External Power Connectors
Extra GPIO
